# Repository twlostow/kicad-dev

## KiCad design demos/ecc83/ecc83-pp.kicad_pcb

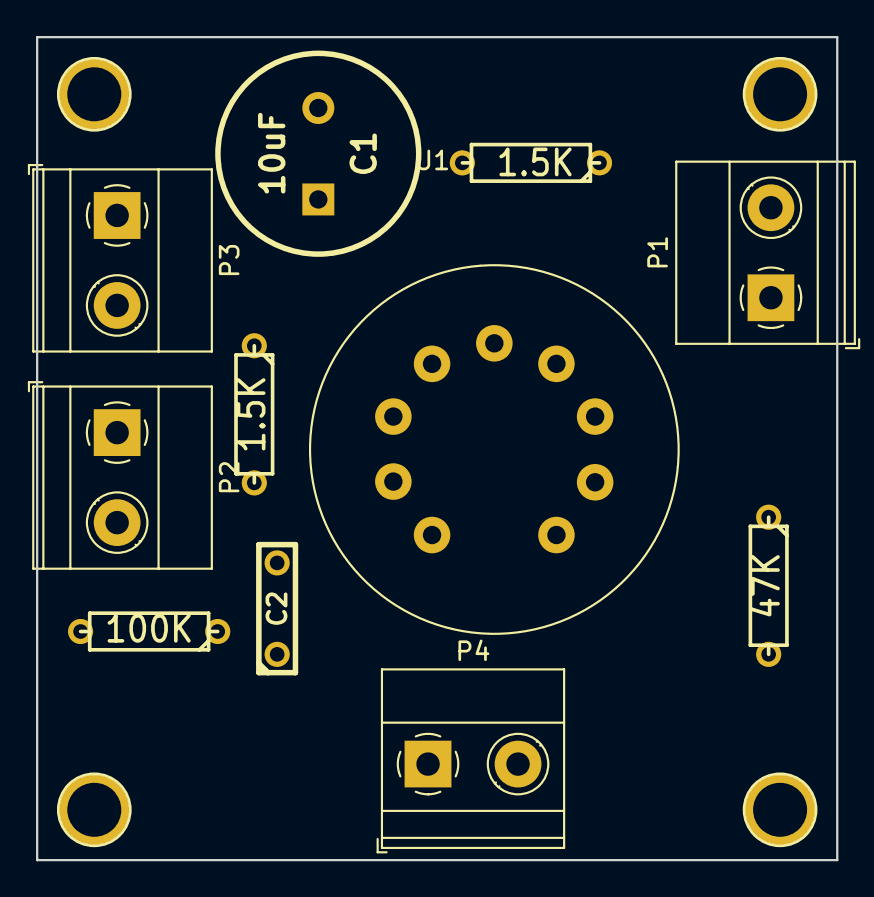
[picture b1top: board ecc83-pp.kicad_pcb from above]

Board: 2 copper layers, 44.5 x 45.7 mm, 15 parts (0 on the bottom side), 9 nets, no tracks yet.

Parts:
C1: 10uF; C2V10
C2: 680nF; C2
P1: IN; TerminalBlock_Phoenix_MKDS-1,5-2_1x02_P5.00mm_Horizontal
P2: OUT; TerminalBlock_Phoenix_MKDS-1,5-2_1x02_P5.00mm_Horizontal
P3: POWER; TerminalBlock_Phoenix_MKDS-1,5-2_1x02_P5.00mm_Horizontal
P4: CONN_2; TerminalBlock_Phoenix_MKDS-1,5-2_1x02_P5.00mm_Horizontal
P5, P6, P7, P8: CONN_1; 1pin
R1, R2: 1.5K; R3
R3: 100K; R3
R4: 47K; R3
U1: ECC83; Valve_ECC-83-1

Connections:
GND: C1.2, P1.1, P2.2, P3.2, R2.2, R3.2, R4.2
unnamed: C1.1, P3.1, U1.6
unnamed: C2.1, P2.1, R3.1
unnamed: C2.2, R1.2, U1.8
unnamed: P1.2, R4.1, U1.2
unnamed: P4.1, U1.9
unnamed: P4.2, U1.4, U1.5
unnamed: R1.1, U1.1, U1.7
unnamed: R2.1, U1.3

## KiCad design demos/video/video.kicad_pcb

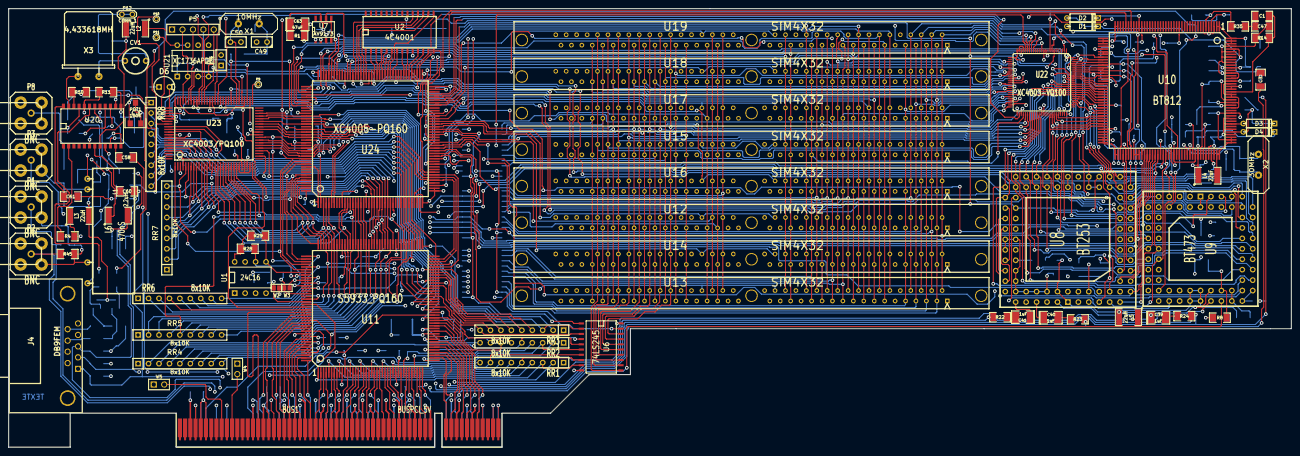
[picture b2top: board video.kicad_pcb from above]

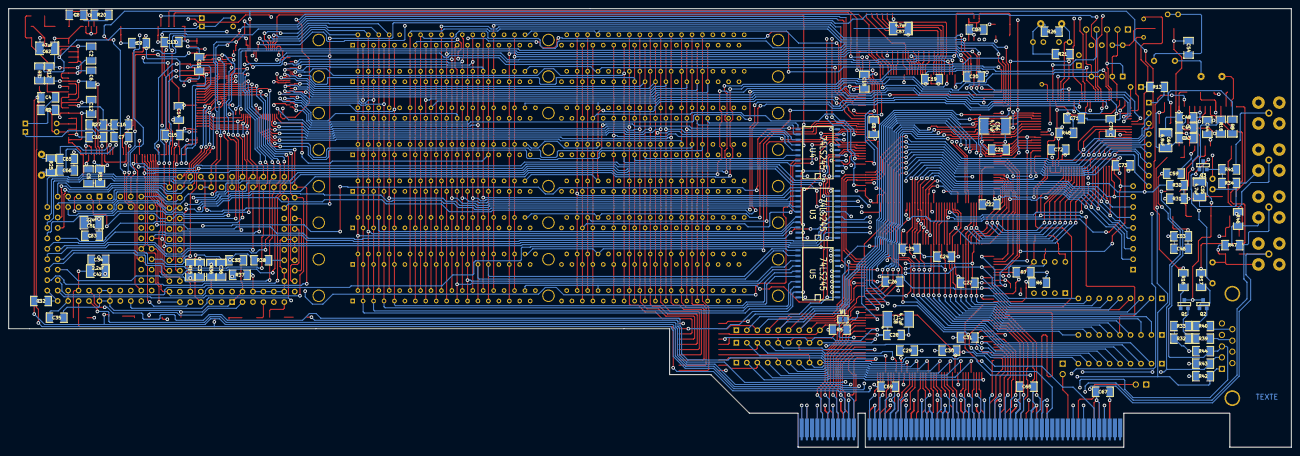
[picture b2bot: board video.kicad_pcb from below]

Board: 4 copper layers, 312.0 x 106.7 mm, 189 parts (103 on the bottom side), 371 nets.

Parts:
BUS1: BUSPCI_5V; BUSPCI
C1, C2, C3, C4, C5, C6, C7, C8, C9, C10, C11, C12, C13, C14, C15, C16, C17, C18, C19, C20, C21, C22, C23, C24, C25, C26, C27, C28, C29, C30, C31, C32, C33, C34, C35, C36, C70, C71, C72, C73: 100nF; SM1206
C37: 100pF; SM1206
C38, C56: 4,7uF; SM1812L
C39, C40, C41: 1uF; SM1210L
C42: 2,2uF; SM1210L
C43, C44, C45: 220nF; SM1206
C46, C47: 220pF; SM1206
C48: 22nF; SM1206
C49, C50: 22pF; C1
C51: 22uF; SM1210L
C52: 22uF; SM1206
C53: 330pF; SM1206
C54, C67, C68, C69: 4,7uF; SM1206
C55, C57: 4,7uF; SM1210L
C58, C59, C60, C61: 47nF; SM1206
C62, C63: 47uF; SM1210L
C64: 6,8uF; SM1210L
C65, C66: 22pF; SM1206
CV1: 5/30pF; CV3-30PF
D1, D2, D3, D4: BAT46; D3
D6: LED; LEDV
J4: DB9FEM; DB9FC
L1: 2,2uH; SM1812
L2, L3, L5: 22uH; SM1812
L4: 22uF; SM1812
L6: 470nS; LRTDK
P1, P2, P3, P8: BNC; SUBCLICK
P4: CONN_2; SIL-2
P5: CONN_5; PIN_ARRAY_5x1
P9, P10, P11: CONN_1; PINTST
P12: CONN_1; TESTPOINT
POT1: 100K; POT_CMS
Q1, Q2, Q3: BC848; SOT23EBC
R1: 10; SM1206
R2, R3: 100; SM1206
R4, R5, R6, R7, R48: 10K; SM1206
R8: 150; SM1206
R9: 150K; SM1206
R10, R11, R12, R13: 1K; SM1206
R14, R15: 1M; SM1206
R16, R17, R18, R19, R20, R21, R22, R23, R24: 220; SM1206
R25, R26: 220K; SM1206
R27: 27K; SM1206
R28, R29: 2,2K; SM1206
R30: 3,3K; SM1206
R31, R32, R33, R34, R35, R36: 470; SM1206
R37, R38: 510; SM1206
R39, R40, R41: 68; SM1206
R42, R43, R44, R45, R46, R47: 75; SM1206
RR1, RR2, RR3, RR6, RR8: 8x10K; SIL-9
RR4, RR5, RR7: 8x10K; r_pack8
U1: 24C16; DIP-8__300
U2: 4C4001; SO28
U3, U4, U5, U6: 74LS245; SO20L
U7: AV9173; SO8E
U8: BT253; PLCC84
U9: BT473; PLCC68
U10: BT812; PQFP160
U11: S5933_PQ160; PQFP160
U12, U13, U14, U15, U16, U17, U18, U19: SIM4X32; sim72
U20: TDA8501; SO24E
U21: XC1736APD8; DIP-8__300
U22: XC4003-VQ100; VQFP100
U23: XC4003/PQ100; PQFP100
U24: XC4005-PQ160; PQFP160
W1: 16/32; GS2
W2: FLOAT#; GS2
W3: SERNV; GS2
W4, W5: TEST; PIN_ARRAY_2X1
X1: 10MHz; HC-18UV
X2: 30MHz; HC-18UV
X3: 4,433618MH; HC-18UH

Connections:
+3.3V: BUS1.A21, BUS1.A27, BUS1.A33, BUS1.A39, BUS1.A45, BUS1.A53, BUS1.B25, BUS1.B31, BUS1.B36, BUS1.B41, BUS1.B43, BUS1.B54, C68.1, C69.1
+5F: C55.1, L3.2, Q1.3, Q2.3, Q3.3
/ESVIDEO-RVB/BLANK-: U9.7, U22.8, U24.53
/ESVIDEO-RVB/BLUE: C60.2, J4.3, R44.2, U9.39
/ESVIDEO-RVB/BLUE_IN: P3.1, R22.1, R46.1
/ESVIDEO-RVB/CLAMP: U8.37, U8.59, U22.7, U24.75
/ESVIDEO-RVB/CSYNCIN-: U8.8, U24.54
/ESVIDEO-RVB/DPC0: RR7.2, U3.2, U8.16, U9.14, U10.92, U11.100, U23.13, U24.21
/ESVIDEO-RVB/DPC1: RR7.3, U3.3, U8.15, U9.15, U10.93, U11.99, U23.12, U24.22
/ESVIDEO-RVB/DPC2: RR7.4, U3.4, U8.14, U9.16, U10.94, U11.98, U23.11, U24.23
/ESVIDEO-RVB/DPC3: RR7.5, U3.5, U8.13, U9.17, U10.95, U11.96, U23.7, U24.24
/ESVIDEO-RVB/DPC4: RR7.6, U3.6, U8.12, U9.18, U10.96, U11.95, U23.9, U24.25
/ESVIDEO-RVB/DPC5: RR7.7, U3.7, U8.11, U9.19, U10.97, U11.94, U23.8, U24.26
/ESVIDEO-RVB/DPC6: RR7.8, U3.8, U8.10, U9.20, U10.99, U11.92, U23.6, U24.27
/ESVIDEO-RVB/DPC7: RR7.9, U3.9, U8.9, U9.21, U10.100, U11.88, U23.5, U24.28
/ESVIDEO-RVB/GREEN: C59.2, J4.2, R43.2, U9.38
/ESVIDEO-RVB/GREEN_IN: C3.2, P2.1, R23.1, R45.1
/ESVIDEO-RVB/OE_PAL-: U9.28, U10.46, U10.47
/ESVIDEO-RVB/OE_RVB-: U8.57, U9.29
/ESVIDEO-RVB/PCA0: U8.17, U9.24, U10.84, U23.65
/ESVIDEO-RVB/PCA1: U8.18, U9.25, U10.85, U23.64
/ESVIDEO-RVB/PCA2: U8.19, U9.26, U23.63
/ESVIDEO-RVB/RDCAD-: U8.20, U23.74
/ESVIDEO-RVB/RDCDA-: U9.22, U23.72
/ESVIDEO-RVB/RED_IN: C4.2, P1.1, R24.1, R47.1
/ESVIDEO-RVB/REF+: R37.2, U8.64, U8.65, U8.66, U8.71, U8.73, U8.76, U8.78, U8.80, U8.82
/ESVIDEO-RVB/TVB0: U8.32, U9.61, U10.55, U22.92
/ESVIDEO-RVB/TVB1: U8.31, U9.62, U10.54, U22.93
/ESVIDEO-RVB/TVB2: U8.30, U9.63, U10.53, U22.94
/ESVIDEO-RVB/TVB3: U8.29, U9.64, U10.52, U22.95
/ESVIDEO-RVB/TVB4: U8.28, U9.65, U10.51, U22.96
/ESVIDEO-RVB/TVB5: U8.27, U9.66, U10.50, U22.97
/ESVIDEO-RVB/TVB6: U8.26, U9.67, U10.49, U22.98
/ESVIDEO-RVB/TVB7: U8.25, U9.68, U10.48, U22.99
/ESVIDEO-RVB/TVG0: U8.48, U9.53, U10.74, U22.67
/ESVIDEO-RVB/TVG1: U8.47, U9.54, U10.73, U22.68
/ESVIDEO-RVB/TVG2: U8.46, U9.55, U10.72, U22.69
/ESVIDEO-RVB/TVG3: U8.45, U9.56, U10.71, U22.70
/ESVIDEO-RVB/TVG4: U8.36, U9.57, U10.70, U22.71
/ESVIDEO-RVB/TVG5: U8.35, U9.58, U10.69, U22.78
/ESVIDEO-RVB/TVG6: U8.34, U9.59, U10.68, U22.80
/ESVIDEO-RVB/TVG7: U8.33, U9.60, U10.67, U22.81
/ESVIDEO-RVB/TVI0: U9.10, U24.108
/ESVIDEO-RVB/TVI1: U9.11, U24.107
/ESVIDEO-RVB/TVR0: U8.56, U9.45, U10.65, U22.82
/ESVIDEO-RVB/TVR1: U8.55, U9.46, U10.64, U22.83
/ESVIDEO-RVB/TVR2: U8.54, U9.47, U10.63, U22.84
/ESVIDEO-RVB/TVR3: U8.53, U9.48, U10.62, U22.85
/ESVIDEO-RVB/TVR4: U8.52, U9.49, U10.61, U22.86
/ESVIDEO-RVB/TVR5: U8.51, U9.50, U10.60, U22.87
/ESVIDEO-RVB/TVR6: U8.50, U9.51, U10.59, U22.90
/ESVIDEO-RVB/TVR7: U8.49, U9.52, U10.58, U22.91
/ESVIDEO-RVB/VAA: C33.1, C34.1, C35.1, C42.1, C51.1, C52.1, L5.2, U8.1, U8.43, U8.44, U8.84, U9.1, U9.2, U9.33, U9.34, U9.35, U9.36
/ESVIDEO-RVB/WRCAD-: U8.24, U23.69
/ESVIDEO-RVB/WRCDA-: U9.23, U23.73
/RAMS/CAS0-: U12.40, U13.40, U14.40, U15.40, U16.40, U17.40, U18.40, U19.40, U24.57
/RAMS/CAS1-: U12.41, U13.41, U14.41, U15.41, U16.41, U17.41, U18.41, U19.41, U24.58
/RAMS/CAS2-: U12.42, U13.42, U14.42, U15.42, U16.42, U17.42, U18.42, U19.42, U24.59
/RAMS/CAS3-: U12.43, U13.43, U14.43, U15.43, U16.43, U17.43, U18.43, U19.43, U24.62
/RAMS/MXA0: U12.12, U13.12, U14.12, U15.12, U16.12, U17.12, U18.12, U19.12, U24.128
/RAMS/MXA1: U12.13, U13.13, U14.13, U15.13, U16.13, U17.13, U18.13, U19.13, U24.127
/RAMS/MXA2: U12.14, U13.14, U14.14, U15.14, U16.14, U17.14, U18.14, U19.14, U24.126
/RAMS/MXA3: U12.15, U13.15, U14.15, U15.15, U16.15, U17.15, U18.15, U19.15, U24.125
/RAMS/MXA4: U12.16, U13.16, U14.16, U15.16, U16.16, U17.16, U18.16, U19.16, U24.124
/RAMS/MXA5: U12.17, U13.17, U14.17, U15.17, U16.17, U17.17, U18.17, U19.17, U24.123
/RAMS/MXA6: U12.18, U13.18, U14.18, U15.18, U16.18, U17.18, U18.18, U19.18, U24.116
/RAMS/MXA7: U12.28, U13.28, U14.28, U15.28, U16.28, U17.28, U18.28, U19.28, U24.115
/RAMS/MXA8: U12.31, U13.31, U14.31, U15.31, U16.31, U17.31, U18.31, U19.31, U24.114
/RAMS/MXA9: U12.32, U13.32, U14.32, U15.32, U16.32, U17.32, U18.32, U19.32, U24.113
/RAMS/MXA10: U12.19, U13.19, U14.19, U15.19, U16.19, U17.19, U18.19, U19.19, U24.109
/RAMS/RAS0-: U19.34, U19.44, U24.74
/RAMS/RAS1-: U18.34, U18.44, U24.73
/RAMS/RAS2-: U17.34, U17.44, U24.69
/RAMS/RAS3-: U15.34, U15.44, U24.68
/RAMS/RAS4-: U16.34, U16.44, U24.67
/RAMS/RAS5-: U12.34, U12.44, U24.66
/RAMS/RAS6-: U14.34, U14.44, U24.65
/RAMS/RAS7-: U13.34, U13.44, U24.64
/RAMS/TVRAM0: U3.18, U12.2, U13.2, U14.2, U15.2, U16.2, U17.2, U18.2, U19.2, U22.17
/RAMS/TVRAM1: U3.17, U12.4, U13.4, U14.4, U15.4, U16.4, U17.4, U18.4, U19.4, U22.19
/RAMS/TVRAM2: U3.16, U12.6, U13.6, U14.6, U15.6, U16.6, U17.6, U18.6, U19.6, U22.20
/RAMS/TVRAM3: U3.15, U12.8, U13.8, U14.8, U15.8, U16.8, U17.8, U18.8, U19.8, U22.18
/RAMS/TVRAM4: U3.14, U12.20, U13.20, U14.20, U15.20, U16.20, U17.20, U18.20, U19.20, U22.28
/RAMS/TVRAM5: U3.13, U12.22, U13.22, U14.22, U15.22, U16.22, U17.22, U18.22, U19.22, U22.29
/RAMS/TVRAM6: U3.12, U12.24, U13.24, U14.24, U15.24, U16.24, U17.24, U18.24, U19.24, U22.31
/RAMS/TVRAM7: U3.11, U12.26, U13.26, U14.26, U15.26, U16.26, U17.26, U18.26, U19.26, U22.32
/RAMS/TVRAM8: U4.18, U12.49, U13.49, U14.49, U15.49, U16.49, U17.49, U18.49, U19.49, U22.33
/RAMS/TVRAM9: U4.17, U12.51, U13.51, U14.51, U15.51, U16.51, U17.51, U18.51, U19.51, U22.34
/RAMS/TVRAM10: U4.16, U12.53, U13.53, U14.53, U15.53, U16.53, U17.53, U18.53, U19.53, U22.35
/RAMS/TVRAM11: U4.15, U12.55, U13.55, U14.55, U15.55, U16.55, U17.55, U18.55, U19.55, U22.36
/RAMS/TVRAM12: U4.14, U12.57, U13.57, U14.57, U15.57, U16.57, U17.57, U18.57, U19.57, U22.39
/RAMS/TVRAM13: U4.13, U12.61, U13.61, U14.61, U15.61, U16.61, U17.61, U18.61, U19.61, U22.40
/RAMS/TVRAM14: U4.12, U12.63, U13.63, U14.63, U15.63, U16.63, U17.63, U18.63, U19.63, U22.41
/RAMS/TVRAM15: U4.11, U12.65, U13.65, U14.65, U15.65, U16.65, U17.65, U18.65, U19.65, U22.42
/RAMS/TVRAM16: U5.18, U12.3, U13.3, U14.3, U15.3, U16.3, U17.3, U18.3, U19.3, U22.43
/RAMS/TVRAM17: U5.17, U12.5, U13.5, U14.5, U15.5, U16.5, U17.5, U18.5, U19.5, U22.44
/RAMS/TVRAM18: U5.16, U12.7, U13.7, U14.7, U15.7, U16.7, U17.7, U18.7, U19.7, U22.45
/RAMS/TVRAM19: U5.15, U12.9, U13.9, U14.9, U15.9, U16.9, U17.9, U18.9, U19.9, U22.46
/RAMS/TVRAM20: U5.14, U12.21, U13.21, U14.21, U15.21, U16.21, U17.21, U18.21, U19.21, U22.47
/RAMS/TVRAM21: U5.13, U12.23, U13.23, U14.23, U15.23, U16.23, U17.23, U18.23, U19.23, U22.48
/RAMS/TVRAM22: U5.12, U12.25, U13.25, U14.25, U15.25, U16.25, U17.25, U18.25, U19.25, U22.53
/RAMS/TVRAM23: U5.11, U12.27, U13.27, U14.27, U15.27, U16.27, U17.27, U18.27, U19.27, U22.54
/RAMS/TVRAM24: U6.18, U12.50, U13.50, U14.50, U15.50, U16.50, U17.50, U18.50, U19.50, U22.55
/RAMS/TVRAM25: U6.17, U12.52, U13.52, U14.52, U15.52, U16.52, U17.52, U18.52, U19.52, U22.56
/RAMS/TVRAM26: U6.16, U12.54, U13.54, U14.54, U15.54, U16.54, U17.54, U18.54, U19.54, U22.57
/RAMS/TVRAM27: U6.15, U12.56, U13.56, U14.56, U15.56, U16.56, U17.56, U18.56, U19.56, U22.58
/RAMS/TVRAM28: U6.14, U12.58, U13.58, U14.58, U15.58, U16.58, U17.58, U18.58, U19.58, U22.59
/RAMS/TVRAM29: U6.13, U12.60, U13.60, U14.60, U15.60, U16.60, U17.60, U18.60, U19.60, U22.60
/RAMS/TVRAM30: U6.12, U12.62, U13.62, U14.62, U15.62, U16.62, U17.62, U18.62, U19.62, U22.61
/RAMS/TVRAM31: U6.11, U12.64, U13.64, U14.64, U15.64, U16.64, U17.64, U18.64, U19.64, U22.62
/RAMS/WRAM-: U12.47, U13.47, U14.47, U15.47, U16.47, U17.47, U18.47, U19.47, U24.63
/buspci.sch/ADR2: U11.68, U23.48, U24.137
/buspci.sch/ADR3: U11.67, U23.44, U24.138
/buspci.sch/ADR4: U11.66, U23.43, U24.139
/buspci.sch/ADR5: U11.64, U23.42, U24.140
/buspci.sch/ADR6: U11.132, U23.39, U24.143
/buspci.sch/BE-0: U11.87, U23.38, U24.144
/buspci.sch/BE-1: U11.63, U23.37, U24.145
/buspci.sch/BE-2: U11.62, U23.36, U24.146
/buspci.sch/BE-3: U11.60, U23.35, U24.147
/buspci.sch/BPCLK: U11.140, U23.30
/buspci.sch/EA1: RR2.6, U11.61
/buspci.sch/EA2: RR3.8, U11.69
/buspci.sch/EA3: RR3.6, U11.73
/buspci.sch/EA4: RR3.2, U11.81
/buspci.sch/EA5: RR4.4, U11.89
/buspci.sch/EA6: RR4.2, U11.97
/buspci.sch/EA7: RR5.9, U11.101
/buspci.sch/EA9: RR5.3, U11.113
/buspci.sch/EA10: RR6.9, U11.121
/buspci.sch/EA11: RR6.7, U11.129
/buspci.sch/EA12: RR6.5, U11.137
/buspci.sch/EA13: RR6.4, U11.141
/buspci.sch/EA14: RR4.8, U11.149
/buspci.sch/EA15: RR4.6, U11.153
/buspci.sch/EQ0: RR1.2, U11.1
/buspci.sch/EQ1: RR1.4, U11.9
/buspci.sch/EQ2: RR1.6, U11.17
/buspci.sch/EQ3: RR1.7, U11.21
/buspci.sch/EQ4: RR1.9, U11.29
/buspci.sch/EQ5: RR2.4, U11.33
/buspci.sch/EQ6: RR2.2, U11.41
/buspci.sch/EQ7: RR2.9, U11.49
/buspci.sch/IRQ-: U11.124, U24.149
/buspci.sch/PTADR-: RR5.5, U11.107, U23.24, U24.14
/buspci.sch/PTATN-: RR5.2, U11.114, U23.18, U24.4
/buspci.sch/PTBE-0: U11.116, U23.20, U24.158
/buspci.sch/PTBE-1: U11.118, U23.21, U24.157
/buspci.sch/PTBE-2: U11.119, U23.22, U24.156
/buspci.sch/PTBE-3: U11.120, U23.23, U24.155
/buspci.sch/PTBURST-: U11.112, U23.17, U24.5
/buspci.sch/PTNUM0: U11.123, U23.34, U24.150
/buspci.sch/PTNUM1: U11.122, U23.32, U24.154
/buspci.sch/PTRDY-: RR6.2, U11.115, U23.19, U24.3
/buspci.sch/PTWR: U11.108, U23.16, U24.12
/buspci.sch/P_AD0: BUS1.A58, U11.56
/buspci.sch/P_AD1: BUS1.B58, U11.55
/buspci.sch/P_AD2: BUS1.A57, U11.54
/buspci.sch/P_AD3: BUS1.B56, U11.52
/buspci.sch/P_AD4: BUS1.A55, U11.48
/buspci.sch/P_AD5: BUS1.B55, U11.47
/buspci.sch/P_AD6: BUS1.A54, U11.46
/buspci.sch/P_AD7: BUS1.B53, U11.44
/buspci.sch/P_AD8: BUS1.B52, U11.42
/buspci.sch/P_AD9: BUS1.A49, U11.40
/buspci.sch/P_AD10: BUS1.B48, U11.39
/buspci.sch/P_AD11: BUS1.A47, U11.38
/buspci.sch/P_AD12: BUS1.B47, U11.36
/buspci.sch/P_AD13: BUS1.A46, U11.35
/buspci.sch/P_AD14: BUS1.B45, U11.34
/buspci.sch/P_AD15: BUS1.A44, U11.32
/buspci.sch/P_AD16: BUS1.A32, U11.14
/buspci.sch/P_AD17: BUS1.B32, U11.12
/buspci.sch/P_AD18: BUS1.A31, U11.8
/buspci.sch/P_AD19: BUS1.B30, U11.7
/buspci.sch/P_AD20: BUS1.A29, U11.6
/buspci.sch/P_AD21: BUS1.B29, U11.4
/buspci.sch/P_AD22: BUS1.A28, U11.3
/buspci.sch/P_AD23: BUS1.B27, U11.2
/buspci.sch/P_AD24: BUS1.A25, U11.158
/buspci.sch/P_AD25: BUS1.B24, U11.156
/buspci.sch/P_AD26: BUS1.A23, U11.155
/buspci.sch/P_AD27: BUS1.B23, U11.154
/buspci.sch/P_AD28: BUS1.A22, U11.152
/buspci.sch/P_AD29: BUS1.B21, U11.148
/buspci.sch/P_AD30: BUS1.A20, U11.147
/buspci.sch/P_AD31: BUS1.B20, U11.146
/buspci.sch/P_C/BE0#: BUS1.A52, U11.43
/buspci.sch/P_C/BE1#: BUS1.B44, U11.28
/buspci.sch/P_C/BE2#: BUS1.B33, U11.15
/buspci.sch/P_C/BE3#: BUS1.B26, U11.159
/buspci.sch/P_CLK: BUS1.B16, U11.142
/buspci.sch/P_DEVSEL#: BUS1.B37, U11.20
/buspci.sch/P_FRAME#: BUS1.A34, U11.16
/buspci.sch/P_GNT#: BUS1.A17, U11.143
/buspci.sch/P_IDSEL: BUS1.A26, U11.160
/buspci.sch/P_INTA#: BUS1.A6, U11.58
/buspci.sch/P_IRDY#: BUS1.B35, U11.18
/buspci.sch/P_LOCK#: BUS1.B39, U11.23
/buspci.sch/P_PAR: BUS1.A43, U11.27
/buspci.sch/P_PERR#: BUS1.B40, U11.24
/buspci.sch/P_REQ#: BUS1.B18, U11.144
/buspci.sch/P_RST#: BUS1.A15, U11.139
/buspci.sch/P_SERR#: BUS1.B42, U11.26
/buspci.sch/P_STOP#: BUS1.A38, U11.22
/buspci.sch/P_TRDY#: BUS1.A36, U11.19
/buspci.sch/RD-: RR3.7, U11.72, U23.46, U24.133
/buspci.sch/RDEMPTY: U11.106, U24.15
/buspci.sch/RDFIFO-: RR5.7, U11.104, U24.16
/buspci.sch/SELECT-: RR3.4, U11.75, U23.45, U24.135
/buspci.sch/WR-: RR3.5, U11.74, U23.47, U24.132
/buspci.sch/WRFIFO-: RR5.8, U11.102, U24.18
/buspci.sch/WRFULL: U11.103, U24.17
/buspci.sch/X_IRQ: RR5.4, U11.109, U24.11
/graphic/14MHZOUT: U7.6, U24.95
/graphic/ACCES_RAM-: U3.19, U4.19, U5.19, U6.19, U22.21, U24.56
/graphic/ACQ_ON: U22.13, U24.48
/graphic/BT812_RD-: U10.86, U23.71
/graphic/BT812_WR-: U10.83, U23.70
/graphic/CADCLK: U8.38, U8.39, U8.40, U22.2, U24.77
/graphic/CCLK: P5.2, U21.2, U23.77
/graphic/CDACLK: U9.9, U22.79, U24.76
/graphic/CLK10MHz: R21.2, U23.57, U24.2
/graphic/CSIO-: U23.61, U24.159
/graphic/CSYNC-OUT: R30.2, U9.8, U22.9, U24.13
/graphic/DIN: P5.3, U21.1, U23.75
/graphic/DONE: P5.4, U23.53
/graphic/F_PALIN: U10.104, U24.43
/graphic/HDOUT: U7.1, U24.7
/graphic/HDREFOUT: U7.2, U24.6
/graphic/HD_PAL-: U10.36, U24.52
/graphic/IA0: U2.6, U24.94
/graphic/IA1: U2.7, U24.92
/graphic/IA2: U2.8, U24.88
/graphic/IA3: U2.9, U24.87
/graphic/IA4: U2.11, U24.86
/graphic/IA5: U2.12, U24.85
/graphic/IA6: U2.13, U24.83
/graphic/IA7: U2.14, U24.78
/graphic/IA8: U2.15, U24.93
/graphic/IA9: U2.5, U24.96
/graphic/ICAS-: U2.17, U24.104
/graphic/ID0: U2.1, U24.102
/graphic/ID1: U2.2, U24.99
/graphic/ID2: U2.18, U24.105
/graphic/ID3: U2.19, U24.106
/graphic/IOE-: U2.16, U24.103
/graphic/IRAS-: U2.4, U24.97
/graphic/IRQ_SLR: RR2.7, U11.57, U24.134
/graphic/IWR-: U2.3, U24.98
/graphic/LED: D6.2, U23.81
/graphic/PROG*: P5.5, U21.3, U21.4, U23.55
/graphic/RESERV1: U23.59, U24.44
/graphic/VD_PAL-: U10.34, U24.37
/graphic/VOSC: C23.1, C63.1, R1.1, U7.4, U7.5, U7.7
/graphic/XTAL_I: C50.1, R26.1, U23.56, X1.2
/graphic/X_CLK: U22.74, U23.86, U24.119
/graphic/X_DIN: U23.85, U24.117
/graphic/X_DONE: U22.50, U23.83, U24.80
/graphic/X_PROG-: U22.52, U23.84, U24.82
/modul/BLEU: C58.2, J4.1, R42.2, U9.37
/modul/CHROM: R16.2, U20.14
/modul/COUT: J4.8, R39.1
/modul/CVBS: R18.2, U20.16
/modul/CVBSOUT: P8.1, R41.1
/modul/LUM: R17.2, U20.19
/modul/YOUT: J4.9, R40.2
/muxdata/DATA_WR: U3.1, U4.1, U5.1, U6.1, U24.55
/muxdata/DPC8: RR8.9, U4.2, U11.86, U23.97, U24.32
/muxdata/DPC9: RR8.8, U4.3, U11.84, U23.96, U24.33
/muxdata/DPC10: RR8.7, U4.4, U11.83, U23.95, U24.34
/muxdata/DPC11: RR8.6, U4.5, U11.82, U23.94, U24.35
/muxdata/DPC12: RR8.5, U4.6, U11.80, U23.93, U24.36
/muxdata/DPC13: RR8.4, U4.7, U11.79, U23.90, U24.45
/muxdata/DPC14: RR8.3, U4.8, U11.78, U23.88, U24.46
/muxdata/DPC15: RR8.2, U4.9, U11.76, U23.89, U24.47
/muxdata/DPC16: RR4.7, U5.2, U11.157
/muxdata/DPC17: RR4.9, U5.3, U11.145
/muxdata/DPC18: RR6.6, U5.4, U11.133
/muxdata/DPC19: RR6.8, U5.5, U11.125
/muxdata/DPC20: RR6.3, U5.6, U11.117
/muxdata/DPC21: RR5.6, U5.7, U11.105
/muxdata/DPC22: RR4.3, U5.8, U11.93
/muxdata/DPC23: RR4.5, U5.9, U11.85
/muxdata/DPC24: RR3.3, U6.2, U11.77
/muxdata/DPC25: RR3.9, U6.3, U11.65
/muxdata/DPC26: RR2.8, U6.4, U11.53
/muxdata/DPC27: RR2.5, U6.5, U11.45
/muxdata/DPC28: RR2.3, U6.6, U11.37
/muxdata/DPC29: RR1.8, U6.7, U11.25
/muxdata/DPC30: RR1.5, U6.8, U11.13
/muxdata/DPC31: RR1.3, U6.9, U11.5
/muxdata/X_DIN: U22.72, U24.118
/pal-ntsc.sch/C-VIDEO: D3.2, D4.1, R2.1, U10.125
/pal-ntsc.sch/RESET-: U10.87, U11.126, U23.1, U24.148
/pal-ntsc.sch/VAF: C2.1, C12.1, C13.1, C14.1, C62.1, L4.2, R12.2, U10.1, U10.2, U10.39, U10.40, U10.41, U10.42, U10.43, U10.78, U10.79, U10.80, U10.81, U10.82, U10.119, U10.120, U10.121, U10.122, U10.123, U10.132, U10.141, U10.142, U10.149, U10.158, U10.159, U10.160
/pal-ntsc.sch/Y-VIDEO: D1.2, D2.1, R3.1, U10.156
/pal-ntsc.sch/Y_SYNC: R20.2, R35.2, U10.6
GND: BUS1.A18, BUS1.A24, BUS1.A30, BUS1.A35, BUS1.A37, BUS1.A42, BUS1.A48, BUS1.A56, BUS1.B3, BUS1.B15, BUS1.B17, BUS1.B22, BUS1.B28, BUS1.B34, BUS1.B38, BUS1.B46, BUS1.B49, BUS1.B57, C2.2, C6.2, C7.2, C9.2, C10.2, C11.2, C12.2, C13.2, C14.2, C15.2, C16.2, C17.2, C18.2, C19.2, C20.2, C21.2, C22.2, C23.2, C24.2, C25.2, C26.2, C27.2, C28.2, C29.2, C30.2, C31.2, C32.1, C33.2, C37.1, C38.2, C43.2, C44.2, C45.2, C46.2, C47.2, C48.1, C49.2, C50.2, C51.2, C52.2, C53.2, C54.2, C55.2, C56.2, C57.2, C62.2, C63.2, C64.2, C65.1, C66.1, C67.2, C68.2, C69.2, C70.2, C71.2, C72.2, C73.2, CV1.2, D1.1, D3.1, J4.4, J4.5, J4.6, J4.7, L6.3, P1.2, P2.2, P3.2, P4.2, P5.1, P8.2, P12.1, POT1.2, POT1.3, R8.2, R14.2, R15.1, R31.1, R32.2, R33.2, R34.2, R37.1, R38.2, R42.1, R43.1, R44.1, R45.2, R46.2, R47.2, U1.1, U1.2, U1.3, U1.4, U2.20, U3.10, U4.10, U5.10, U6.10, U7.3, U8.2, U8.3, U8.21, U8.22, U8.23, U8.41, U8.42, U8.61, U8.63, U8.67, U9.3, U9.4, U9.12, U9.13, U9.31, U9.32, U10.3, U10.5, U10.7, U10.16, U10.30, U10.44, U10.56, U10.66, U10.75, U10.88, U10.89, U10.90, U10.98, U10.103, U10.111, U10.116, U10.118, U10.124, U10.126, U10.128, U10.130, U10.134, U10.136, U10.138, U10.139, U10.143, U10.145, U10.147, U10.151, U10.153, U10.155, U10.157, U11.10, U11.30, U11.50, U11.70, U11.90, U11.110, U11.130, U11.150, U12.1, U12.39, U12.72, U13.1, U13.39, U13.72, U14.1, U14.39, U14.72, U15.1, U15.39, U15.72, U16.1, U16.39, U16.72, U17.1, U17.39, U17.72, U18.1, U18.39, U18.72, U19.1, U19.39, U19.72, U20.10, U20.17, U21.5, U22.1, U22.11, U22.23, U22.38, U22.49, U22.64, U22.77, U22.88, U23.4, U23.14, U23.26, U23.41, U23.52, U23.67, U23.80, U23.91, U24.1, U24.10, U24.19, U24.29, U24.39, U24.51, U24.61, U24.70, U24.79, U24.91, U24.101, U24.110, U24.122, U24.131, U24.141, U24.151, W1.1, W2.1, W3.1, W4.1, W5.1
unnamed: BUS1.A4, BUS1.B4
unnamed: BUS1.B9, W5.2
unnamed: BUS1.B11, W4.2
unnamed: C1.1, C47.1, R35.1
unnamed: C1.2, R14.1, U10.140
unnamed: C3.1, R3.2
unnamed: C4.1, R2.2
unnamed: C5.1, U10.117
unnamed: C5.2, R19.1
unnamed: C6.1, R12.1, U10.113, U10.137, U10.144
unnamed: C7.1, R27.2, U10.114
unnamed: C8.1, U10.4
unnamed: C8.2, R20.1
unnamed: C16.1, U10.110
unnamed: C32.2, U9.43, U9.44
unnamed: C34.2, C42.2, R8.1, U9.40
unnamed: C35.2, U9.41, U9.42
unnamed: C36.1, R15.2, U8.7
unnamed: C36.2, C37.2, R36.1
unnamed: C39.1, U8.83
unnamed: C39.2, R24.2
unnamed: C40.1, U8.79
unnamed: C40.2, R23.2
unnamed: C41.1, U8.75
unnamed: C41.2, R22.2
unnamed: C43.1, U20.12
unnamed: C44.1, U20.6
unnamed: C45.1, U20.15
unnamed: C46.1, C53.1, L1.2
unnamed: C48.2, C64.1, R11.2, U20.13
unnamed: C49.1, R21.1, R26.2, X1.1
unnamed: C54.1, L2.2, U20.8
unnamed: C58.1, U20.11
unnamed: C59.1, U20.9
unnamed: C60.1, U20.7
unnamed: C61.1, R30.1, R31.2
unnamed: C61.2, U20.24
unnamed: C65.2, R25.2, U10.109, X2.1
unnamed: C66.2, R25.1, U10.108, X2.2
unnamed: CV1.1, X3.1
unnamed: D6.1, R13.2
unnamed: L1.1, U20.18
unnamed: L6.1, R10.1
unnamed: L6.2, R11.1, U20.20
unnamed: P4.1, R48.2, U23.25, U23.27, U23.29
unnamed: P9.1, U23.51
unnamed: P10.1, U23.87
unnamed: P11.1, U23.82
unnamed: POT1.1, R9.1
unnamed: Q1.1, R32.1, R39.2
unnamed: Q1.2, R16.1
unnamed: Q2.1, R33.1, R40.1
unnamed: Q2.2, R17.1
unnamed: Q3.1, R34.1, R41.2
unnamed: Q3.2, R18.1
unnamed: R4.1, U20.2
unnamed: R5.1, U11.59, W1.2
unnamed: R6.1, U11.138, W2.2
unnamed: R7.1, U11.135, W3.2
unnamed: R9.2, U20.21
unnamed: R10.2, U20.22
unnamed: R19.2, U10.115
unnamed: R27.1, U10.135
unnamed: R28.2, U1.6, U11.128
unnamed: R29.2, U1.5, U11.127
unnamed: R36.2, U8.6
unnamed: R38.1, U8.69
unnamed: U8.58, U8.68
unnamed: U8.60, U8.70
unnamed: U8.62, U8.72
unnamed: U20.23, X3.2
VCC: BUS1.A5, BUS1.A8, BUS1.A10, BUS1.A16, BUS1.A59, BUS1.A61, BUS1.A62, BUS1.B5, BUS1.B6, BUS1.B19, BUS1.B59, BUS1.B61, BUS1.B62, C9.1, C10.1, C11.1, C15.1, C17.1, C18.1, C19.1, C20.1, C21.1, C22.1, C24.1, C25.1, C26.1, C27.1, C28.1, C29.1, C30.1, C31.1, C38.1, C56.1, C57.1, C67.1, C70.1, C71.1, C72.1, C73.1, D2.2, D4.2, L2.1, L3.1, L4.1, L5.1, R1.2, R4.2, R5.2, R6.2, R7.2, R13.1, R28.1, R29.1, R48.1, RR1.1, RR2.1, RR3.1, RR4.1, RR5.1, RR6.1, RR7.1, RR8.1, U1.7, U1.8, U2.10, U3.20, U4.20, U5.20, U6.20, U10.31, U10.45, U10.57, U10.76, U10.91, U10.102, U10.112, U11.11, U11.31, U11.51, U11.71, U11.91, U11.111, U11.131, U11.151, U12.10, U12.30, U12.59, U13.10, U13.30, U13.59, U14.10, U14.30, U14.59, U15.10, U15.30, U15.59, U16.10, U16.30, U16.59, U17.10, U17.30, U17.59, U18.10, U18.30, U18.59, U19.10, U19.30, U19.59, U21.7, U21.8, U22.12, U22.22, U22.24, U22.25, U22.26, U22.37, U22.51, U22.63, U22.75, U22.89, U22.100, U23.3, U23.15, U23.28, U23.40, U23.54, U23.66, U23.78, U23.92, U24.20, U24.38, U24.40, U24.41, U24.42, U24.60, U24.81, U24.100, U24.120, U24.142, U24.160

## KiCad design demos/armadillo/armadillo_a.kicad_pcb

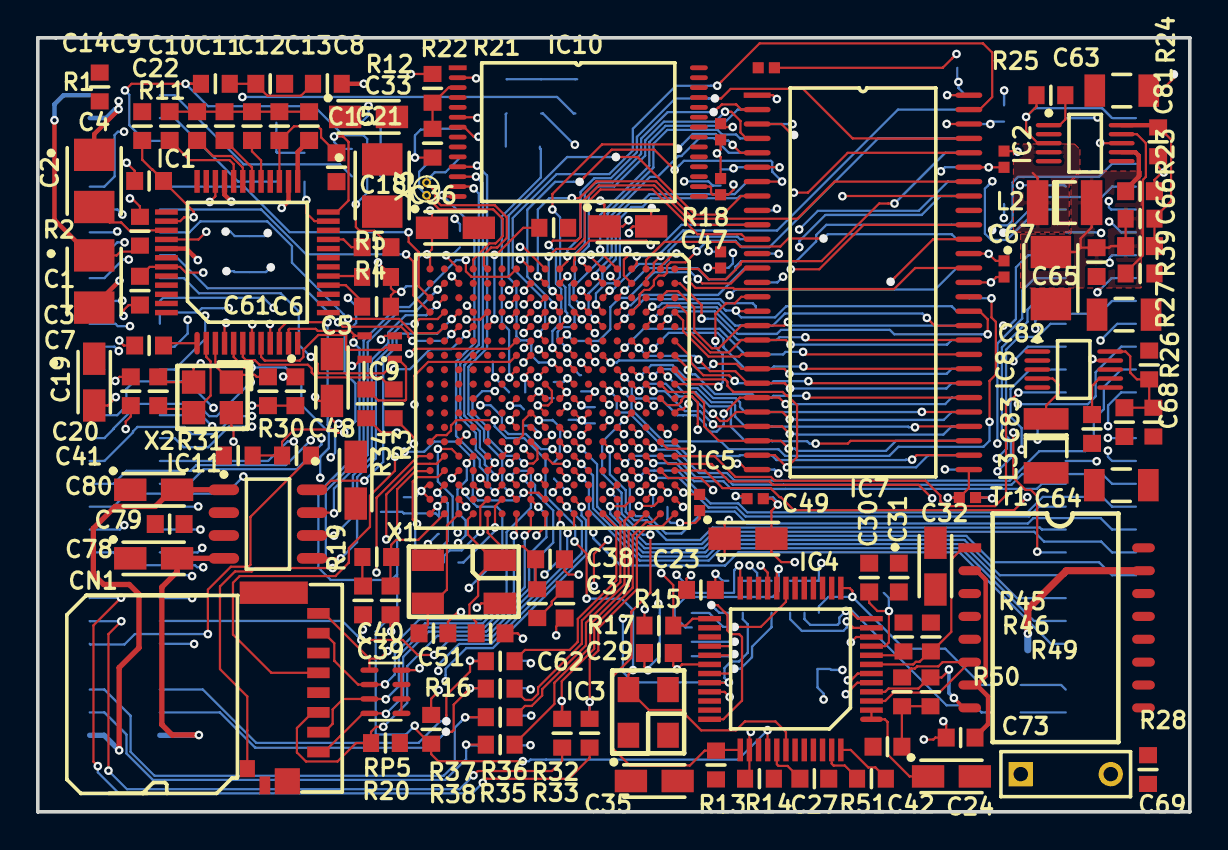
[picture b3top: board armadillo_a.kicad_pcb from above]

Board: 6 copper layers, 64.0 x 43.0 mm, 178 parts (0 on the bottom side), 260 nets.

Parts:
C1, C2, C21: 100u 6.3v; CAPMP3528X210N
C3, C4, C6, C7, C8, C13, C14, C18, C20, C23, C26, C27, C29, C30, C31, C34, C42, C65, C72, C73, C79, C81, C83: 100n; CAPC1608X87N
C5, C19, C24, C32, C33, C35: 10u/16V; CAPMP3216X180N
C9, C10, C11, C12: 270p; CAPC1608X87N
C15, C16, C17: 1u; CAPC1608X87N
C22: 10u x5r; CAPC1608X87N
C36, C47, C48, C49: 22u; CAPMP3216X180N
C37: 4.7n; CAPC1608X87N
C38: 470p; CAPC1608X87N
C39: 10n; CAPC1608X87N
C40: 1n; CAPC1608X87N
C41, C51, C61, C62: 22p; CAPC1608X87N
C43, C44, C45, C46, C50, C52, C53, C55, C57, C58, C60, C99, C102, C104, C136, C149, C150, C159, C162, C166, C167, C172, C173, C180, C181, C182, C188, C189, C190: 100n; CAPC1005X55N
C54, C56, C70, C71: 15p; CAPC1608X87N
C59: 1n; CAPC1005X55N
C63, C64, C82: 10u X7R; CAPC3216X140N
C66, C68: 33p; CAPC1608X87N
C67: 47u; CAPMP3528X210N
C69: 100n/100V; CAPR500-250X720X650
C78, C80: 22u 10V; CAPMP3216X180N
CN1: microSD card; SD_CARD_47309-2651_MOLEX
CN2, CN3: PBHTD60S; PLHTD60S-GC
D20, D21, D23, D24: 4148; CD2012-0805
IC1: AD1981B; LQFP48L
IC2, IC8: TPS62000DGS; TSSOP50P490-10AL
IC3: XO53050UITA 50 MHz; XTAL_XO53
IC4: DM9161AEP; LQFP48l
IC5: AT91SAM9263-CU; TFBGA324
IC6, IC7: MT48LC16M16A2TG; TSOP54
IC9: SN74LVC1G66DCKR; TI_DCK5
IC10: MEM_AT45DB642; TSOP28-1
IC11: SP2526; SOIC127P600-8AL
L1: 4.7 uH 220 mA; 3261
L2: 10 uH LQH43CN100K03L; INDC3225-1210
L3: 15 uH LQH43CN150K03L; INDC3225-1210
L4, L9: Inductor; INDC1608-0603
R1, R2: 1k; RESC1608X55N
R3, R34: 47; RESC1608X55N
R4, R5: 2.2k; RESC1608X55N
R6, R7, R8, R9: 4.7k; RESC1608X55N
R10: 0; RESC2012X60N
R11: 3.9k; RESC1608X55N
R12, R41, R42: 470; RESC1608X55N
R13, R14, R16, R20, R21: 10k; RESC1608X55N
R15, R19: 1.5k; RESC1608X55N
R17: 2k; RESC1608X55N
R18, R22: 0*; RESC1608X55N
R23: 165k; RESC1608X55N
R24, R27: 100k; RESC1608X55N
R25, R39: 330k; RESC1608X55N
R26: 630k; RESC1608X55N
R28, R29: 75; RESC1608X55N
R30, R40, R43, R44, R47: 15k; RESC1608X55N
R31: 22k; RESC1608X55N
R32, R33: 27; RESC1608X55N
R35, R36, R37, R38: 39; RESC1608X55N
R45, R46, R49, R50: 49.9; RESC1608X55N
R51: 6.8k; RESC1608X55N
R117: 0; RESC3216X65N
RP1, RP2, RP3, RP4: RAC4X101 10k; CAY-16
RP5: RAC4X101 68k; CAY-16
Tr1: TR_H1260NL; H1260NL
X1: 18.432 MHz; XTALL_ABM3
X2: CFPX-180 24.576 MHz; XTALL_CFPX_180
X3: 32768 Hz; XTAL_32k

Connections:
+1V2: C36.1, C49.1, C65.2, C66.2, C67.1, C99.2, C102.2, C104.2, IC5.A16, IC5.H10, IC5.V1, L2.2, R18.1, R23.2
+3V3: C5.1, C6.2, C7.1, C23.2, C27.2, C29.2, C34.2, C35.1, C44.2, C45.2, C46.2, C47.1, C48.1, C50.2, C52.2, C53.2, C55.2, C58.2, C60.2, C64.2, C68.2, C136.2, C149.2, C150.2, C159.2, C162.2, C166.2, C167.2, C172.2, C173.2, C180.2, C181.2, C182.2, C188.2, C189.2, C190.2, CN1.P4, D24.1, IC1.1, IC1.9, IC3.1, IC3.4, IC4.23, IC4.30, IC4.41, IC5.A17, IC5.C17, IC5.H8, IC5.K10, IC5.K12, IC5.L8, IC5.L9, IC5.L10, IC5.L11, IC5.M10, IC5.M13, IC5.T1, IC5.T2, IC6.1, IC6.3, IC6.9, IC6.14, IC6.27, IC6.43, IC6.49, IC7.1, IC7.3, IC7.9, IC7.14, IC7.27, IC7.43, IC7.49, IC9.5, IC10.2, IC10.6, IC10.16, L3.2, L9.1, R15.1, R16.2, R20.2, R21.1, R26.2, RP2.1, RP2.2, RP2.3, RP3.1, RP3.2, RP3.3, RP3.4, RP4.5, RP4.6, RP4.7, RP4.8, RP5.1, RP5.2, RP5.3, RP5.4
A0: IC5.E9, IC6.15
A1: IC5.A9, IC7.15
A2: IC5.D9, IC6.23, IC7.23
A3: IC5.C9, IC6.24, IC7.24
A4: IC5.B9, IC6.25, IC7.25
A5: IC5.A8, IC6.26, IC7.26
A6: IC5.F9, IC6.29, IC7.29
A7: IC5.B8, IC6.30, IC7.30
A8: IC5.C8, IC6.31, IC7.31
A9: IC5.D8, IC6.32, IC7.32
A10: IC5.A7, IC6.33, IC7.33
A11: IC5.A6, IC6.34, IC7.34
A13: IC5.C7, IC6.35, IC7.35
A14: IC5.E7, IC6.36, IC7.36
A16: IC5.F7, IC6.20, IC7.20
A17: IC5.D6, IC6.21, IC7.21
ACGND: C3.1, C4.2, C8.2, C9.2, C10.2, C11.2, C12.2, C13.2, C14.2, C15.2, C21.2, C22.1, C33.2, CN2.52, CN2.53, CN2.59, CN2.60, IC1.26, IC1.33, IC1.40, IC1.44, R1.1, R2.1, R6.2, R7.2, R10.2
ACVDD: C3.2, C4.1, C8.1, C14.1, C21.1, C33.1, IC1.25, IC1.34, IC1.38, IC1.43, L1.2, R12.1
AUDIO_HPOUT_L: C2.2, CN2.55, R1.2
AUDIO_HPOUT_R: C1.2, CN2.57, R2.2
AUDIO_LINE_IN_L: CN2.56, R9.2
AUDIO_LINE_IN_R: CN2.58, R8.1
AUDIO_MIC_IN: C18.2, CN2.54, R11.2
CAS: IC5.B3, IC6.17, IC7.17
D0: IC5.C2, IC6.2
D1: IC5.D4, IC6.4
D2: IC5.A1, IC6.5
D3: IC5.D2, IC6.7
D4: IC5.B1, IC6.8
D5: IC5.E3, IC6.10
D6: IC5.C1, IC6.11
D7: IC5.E2, IC6.13
D8: IC5.E4, IC6.42
D9: IC5.F3, IC6.44
D10: IC5.D1, IC6.45
D11: IC5.F4, IC6.47
D12: IC5.F5, IC6.48
D13: IC5.F2, IC6.50
D14: IC5.G4, IC6.51
D15: IC5.E1, IC6.53
D16: IC5.H7, IC7.2
D17: IC5.G1, IC7.4
D18: IC5.J5, IC7.5
D19: IC5.J4, IC7.7
D20: IC5.J8, IC7.8
D21: IC5.J7, IC7.10
D22: IC5.J3, IC7.11
D23: IC5.J6, IC7.13
D24: IC5.H1, IC7.42
D25: IC5.K8, IC7.44
D26: IC5.J2, IC7.45
D27: IC5.K5, IC7.47
D28: IC5.K2, IC7.48
D29: IC5.K7, IC7.50
D30: IC5.J1, IC7.51
D31: IC5.K6, IC7.53
DRXD: CN3.42, IC5.A11
DTXD: CN3.44, IC5.E10
ETH100_AGND: C24.2, C26.2, C30.2, C31.2, C32.2, C42.1, C69.1, C72.2, C73.2, IC4.5, IC4.6, IC4.46, R117.2
ETH_LED1: CN3.3, R41.2
ETH_LED2: CN3.5, R42.2
ETH_RX+: CN3.6, Tr1.11
ETH_RX-: CN3.4, Tr1.9
ETH_TX+: CN3.12, Tr1.14
ETH_TX-: CN3.10, Tr1.16
EXT_VDD_5V: C19.1, C20.2, C63.2, C79.2, C82.2, CN3.57, CN3.58, CN3.59, CN3.60, IC2.1, IC2.6, IC8.1, IC8.6, IC11.7, L1.1, R25.2, R39.2
GND: C5.2, C6.1, C7.2, C19.2, C20.1, C23.1, C27.1, C29.1, C34.1, C35.2, C36.2, C37.1, C38.1, C39.1, C40.1, C41.1, C43.1, C44.1, C45.1, C46.1, C47.2, C48.2, C49.2, C50.1, C51.1, C52.1, C53.1, C54.1, C55.1, C56.1, C57.1, C58.1, C59.1, C60.1, C61.1, C62.1, C63.1, C64.1, C65.1, C67.2, C70.1, C71.1, C78.2, C79.1, C80.2, C81.1, C82.1, C83.1, C99.1, C102.1, C104.1, C136.1, C149.1, C150.1, C159.1, C162.1, C166.1, C167.1, C172.1, C173.1, C180.1, C181.1, C182.1, C188.1, C189.1, C190.1, CN1.G1, CN1.G2, CN1.G3, CN1.P6, CN2.7, CN2.8, CN2.15, CN2.31, CN2.32, CN2.51, CN3.1, CN3.2, CN3.7, CN3.8, CN3.14, CN3.27, CN3.30, CN3.51, CN3.53, CN3.54, IC1.4, IC1.7, IC2.3, IC2.7, IC2.10, IC3.2, IC4.10, IC4.15, IC4.33, IC4.39, IC4.44, IC5.C16, IC5.G8, IC5.G10, IC5.G11, IC5.G12, IC5.H9, IC5.H11, IC5.J9, IC5.J10, IC5.J11, IC5.K9, IC5.K11, IC5.L12, IC5.M11, IC5.M12, IC5.N13, IC5.N14, IC5.T17, IC5.V16, IC5.V17, IC6.6, IC6.12, IC6.28, IC6.41, IC6.46, IC6.52, IC6.54, IC7.6, IC7.12, IC7.28, IC7.41, IC7.46, IC7.52, IC7.54, IC8.3, IC8.7, IC8.10, IC9.3, IC10.7, IC11.6, R4.1, R5.1, R10.1, R13.1, R14.1, R22.1, R24.1, R27.1, R31.2, R40.2, R43.1, R44.1, R47.1, R117.1, RP1.1, RP1.2, RP1.3, RP1.4, X1.2, X1.4, X2.2, X2.4
JNTRST: IC5.U16, RP4.2
JRTCK: IC5.U15, RP4.1
JTDI: IC5.P17, RP4.3
JTMS: IC5.N17, RP4.4
NRST: CN3.55, IC1.11, IC4.40, IC5.V15, IC8.4, IC9.4, R16.1
NetC1_1: C1.1, IC1.41
NetC2_1: C2.1, IC1.39
NetC9_1: C9.1, IC1.32
NetC10_1: C10.1, IC1.31
NetC11_1: C11.1, IC1.30
NetC12_1: C12.1, IC1.29
NetC13_1: C13.1, C15.1, IC1.27
NetC16_1: C16.1, IC1.24
NetC16_2: C16.2, R7.1, R8.2
NetC17_1: C17.1, IC1.23
NetC17_2: C17.2, R6.1, R9.1
NetC18_1: C18.1, IC1.21
NetC22_2: C22.2, R11.1, R12.2
NetC24_1: C24.1, C26.1, IC4.1, IC4.2, L4.2
NetC30_1: C30.1, C32.1, C72.1, C73.1, IC4.9, L4.1, Tr1.2, Tr1.7
NetC31_1: C31.1, R45.2, R46.2
NetC37_2: C37.2, R17.1
NetC38_2: C38.2, IC5.P18, R17.2
NetC39_2: C39.2, R19.1
NetC40_2: C40.2, IC5.U18, R19.2
NetC41_2: C41.2, IC1.2, X2.3
NetC42_2: C42.2, R49.1, R50.1
NetC43_2: C43.2, D21.2, IC5.M8
NetC51_2: C51.2, IC5.T18, X1.3
NetC54_2: C54.2, IC5.R1, X3.2
NetC56_2: C56.2, IC5.P1, X3.1
NetC57_2: C57.2, C59.2, IC5.U17, IC5.V18, L9.2
NetC61_2: C61.2, IC1.3, X2.1
NetC62_2: C62.2, IC5.R18, X1.1
NetC66_1: C66.1, IC2.5, R23.1, R24.2
NetC68_1: C68.1, IC8.5, R26.1, R27.2
NetC69_2: C69.2, R28.1, R29.1
NetC70_2: C70.2, IC5.B18, R32.2
NetC71_2: C71.2, IC5.A18, R33.2
NetC81_2: C81.2, IC2.2
NetC83_2: C83.2, IC8.2
NetCN1_G4: CN1.G4, IC5.M1
NetCN1_P1: CN1.P1, IC5.L17, RP5.8
NetCN1_P2: CN1.P2, IC5.L18, RP5.7
NetCN1_P3: CN1.P3, IC5.M16, R20.1
NetCN1_P5: CN1.P5, IC5.M14
NetCN1_P7: CN1.P7, IC5.M18, RP5.6
NetCN1_P8: CN1.P8, IC5.L15, RP5.5
NetD20_1: D20.1, D23.2, D24.2
NetD20_2: D20.2, D21.1
NetIC1_5: IC1.5, IC5.K18
NetIC1_6: IC1.6, R3.2
NetIC1_8: IC1.8, IC9.2
NetIC1_10: IC1.10, IC5.K17
NetIC1_16: IC1.16, R4.2
NetIC1_17: IC1.17, R5.2
NetIC2_4: IC2.4, IC8.8, R39.1
NetIC2_9: IC2.9, L2.1
NetIC3_3: IC3.3, IC4.42, IC5.V13
NetIC4_3: IC4.3, R50.2, Tr1.6
NetIC4_4: IC4.4, R49.2, Tr1.8
NetIC4_7: IC4.7, R45.1, Tr1.1
NetIC4_8: IC4.8, R46.1, Tr1.3
NetIC4_11: IC4.11, RP2.8
NetIC4_12: IC4.12, R41.1, RP2.7
NetIC4_13: IC4.13, R42.1, RP2.6
NetIC4_19: IC4.19, IC5.V14, RP1.5
NetIC4_20: IC4.20, IC5.T13, RP1.6
NetIC4_21: IC4.21, IC5.P16
NetIC4_24: IC4.24, IC5.T15
NetIC4_25: IC4.25, IC5.R16, R15.2
NetIC4_28: IC4.28, IC5.R14, RP1.7
NetIC4_29: IC4.29, IC5.T14, RP1.8
NetIC4_31: IC4.31, RP3.5
NetIC4_32: IC4.32, IC5.T16, RP3.7
NetIC4_36: IC4.36, RP3.8
NetIC4_37: IC4.37, IC5.D11, R13.2
NetIC4_38: IC4.38, IC5.U14, R14.2
NetIC4_47: IC4.47, R51.2
NetIC4_48: IC4.48, R51.1
NetIC5_B5: IC5.B5, IC7.39
NetIC5_C18: IC5.C18, R35.2
NetIC5_D18: IC5.D18, R36.2
NetIC5_E5: IC5.E5, IC6.39
NetIC5_E18: IC5.E18, R37.2
NetIC5_F18: IC5.F18, R38.2
NetIC5_K13: IC5.K13, R34.1
NetIC5_K16: IC5.K16, R3.1
NetIC5_M17: IC5.M17, IC10.11
NetIC5_N15: IC5.N15, IC10.13
NetIC5_N16: IC5.N16, IC10.14
NetIC5_P5: IC5.P5, R18.2
NetIC5_P15: IC5.P15, IC10.12
NetIC8_9: IC8.9, L3.1
NetIC9_1: IC9.1, R34.2
NetIC10_3: IC10.3, R21.2, R22.2
NetR28_2: R28.2, Tr1.10
NetR29_2: R29.2, Tr1.15
PA13: CN2.19, IC5.L13
PA14: CN2.21, IC5.K14
PA26: CN2.44, IC5.T5
PA27: CN2.50, IC5.V3
PA28: CN2.46, IC5.U5
PA29: CN2.48, IC5.V4
PA30: CN2.42, IC5.R5
PB4: CN2.23, IC5.L14
PB5: CN2.16, IC5.J15
PB6: CN2.20, IC5.J16
PB7: CN2.14, IC5.J17
PB8: CN2.18, IC5.J18
PB9: CN2.24, IC5.J13
PB10: CN2.22, IC5.J14
PB11: CN2.26, IC5.J12
PB12: CN2.12, IC5.H18
PB13: CN3.11, IC5.H15
PB14: CN2.10, IC5.H17
PB15: CN3.13, IC5.H14
PB16: CN2.17, IC5.B17
PB17: CN3.15, IC5.H13
PB18: CN3.9, IC5.G18
PC0: CN3.18, IC5.E16
PC1: CN3.16, IC5.D17
PC2: CN3.20, IC5.D16
PC3: CN3.21, IC5.C15
PC4: CN3.24, IC5.E14
PC5: CN3.26, IC5.B16
PC6: CN3.33, IC5.D13
PC7: CN3.25, IC5.B15
PC8: CN3.23, IC5.C14
PC9: CN3.29, IC5.B14
PC10: CN3.22, IC5.D15
PC11: CN3.35, IC5.E13
PC12: CN3.28, IC5.A15
PC13: CN3.19, IC5.F13
PC14: CN3.34, IC5.C13
PC15: CN3.41, IC5.E12
PC16: CN3.32, IC5.D14
PC17: CN3.36, IC5.B13
PC18: CN3.17, IC5.F12
PC19: CN3.31, IC5.A14
PC20: CN3.39, IC5.D12
PC21: CN3.37, IC5.B12
PD0: CN3.38, IC5.B10
PD1: CN3.40, IC5.D10
PD2: CN3.43, IC5.C10
PD3: CN3.46, IC5.F10
PD5: CN3.45, IC5.G5
PD6: CN3.48, IC5.G3
PD7: CN3.47, IC5.F1
PD8: CN3.50, IC5.G6
PD9: CN3.49, IC5.H4
PD10: CN3.52, IC5.G7
PE0: CN2.41, IC5.K3
PE1: CN2.39, IC5.K4
PE2: CN2.25, IC5.L6
PE3: CN2.28, IC5.L7
PE4: CN2.45, IC5.L2
PE5: CN2.29, IC5.L5
PE6: CN2.47, IC5.K1
PE7: CN2.35, IC5.L4
PE8: CN2.30, IC5.M7
PE9: CN2.38, IC5.L3
PE10: CN2.43, IC5.L1
PE11: CN2.37, IC5.M4
PE12: CN2.27, IC5.M6
PE13: CN2.33, IC5.M5
PE14: CN2.34, IC5.M2
PE15: CN2.36, IC5.M3
PSU_EN: CN3.56, IC2.8, R25.1
RAS: IC5.B4, IC6.18, IC7.18
SDA10: IC5.E8, IC6.22, IC7.22
SDCK: IC5.C5, IC6.38, IC7.38
SDCKE: IC5.A2, IC6.37, IC7.37
SDCS: IC5.A4, IC6.19, IC7.19
SDWE: IC5.C4, IC6.16, IC7.16
UENA: IC5.U4, IC11.1
UENB: IC5.T4, IC11.4
UFLGA: IC5.U3, IC11.2
UFLGB: IC5.U2, IC11.3
USBCNX: IC5.R4, R30.2, R31.1
USB_HOST_A_5V: C78.1, CN2.2, IC11.8
USB_HOST_A_N: CN2.6, R38.1, R44.2
USB_HOST_A_P: CN2.4, R37.1, R47.2
USB_HOST_B_5V: C80.1, CN2.1, IC11.5
USB_HOST_B_N: CN2.5, R36.1, R40.1
USB_HOST_B_P: CN2.3, R35.1, R43.2
USB_SLAVE_5V: CN2.9, R30.1
USB_SLAVE_D_N: CN2.11, R32.1
USB_SLAVE_D_P: CN2.13, R33.1
VBAT: CN2.49, D23.1
WKUP: CN2.40, IC5.P4
